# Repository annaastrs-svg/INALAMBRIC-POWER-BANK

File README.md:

-  FLUX CASE ! -

this is an inalambric power bank that uses a coil and inductance theory for charging my iphone LOL

I made this project because moustly I dont have battery or a cable, sooo a power bank that does not need non of them is the soloution yeyy 

PAG OF FLUX CASE (fotos , tutorial and more)
https://annaastrs-svg.github.io/Flux-Page-/

--

- PCB -

-eschematic -

-pcb -

-3d-

-BOM -

- CAD -

- 

WIRES ! 

MH-CD42 - USBC . 
VIN - VBUS ,
GND - GND ,

MH-CD42 - BTN . 
KEY - (+) , 
GND - (-) ,

MH-CD42 - COIL . 
VOUT - (+) ,
GND - (-) ,

MH-CD42 - BATTERY .
BAT - (+) , 
GND - (-) ,

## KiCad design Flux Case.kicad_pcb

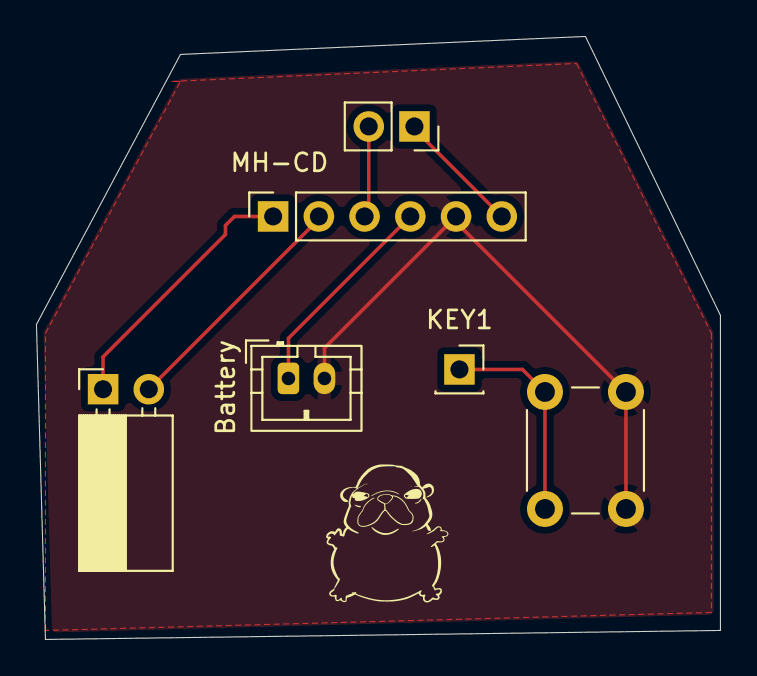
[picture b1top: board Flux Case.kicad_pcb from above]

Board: 2 copper layers, 38.0 x 33.5 mm, 6 parts (0 on the bottom side), 7 nets.

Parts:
Battery: Battery_Cell; JST_PH_B2B-PH-K_1x02_P2.00mm_Vertical
J1: USBC; PinSocket_1x02_P2.54mm_Horizontal
J2: Qi; PinSocket_1x02_P2.54mm_Vertical
KEY1: Conn_01x01_Pin; PinSocket_1x01_P2.54mm_Vertical
MH-CD: Conn_01x06; PinSocket_1x06_P2.54mm_Vertical
SW1: SW_Push; SW_PUSH_6mm_H4.3mm

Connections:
unnamed: Battery.1 (+), MH-CD.4
unnamed: Battery.2 (-), MH-CD.5, SW1.1
unnamed: J1.1, MH-CD.1
unnamed: J1.2, MH-CD.2
unnamed: J2.1, MH-CD.6
unnamed: J2.2, MH-CD.3
unnamed: KEY1.1 (Pin_1_1), SW1.2

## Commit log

2026-06-02 PCB DESIGN
2026-06-02 Add README for inalambric power bank project
    Added detailed description of the inalambric power bank project, including components, wiring instructions, and CAD image.
2026-06-02 Create tutorial for assembling power bank
    Added detailed building tutorial for power bank assembly and testing procedures.
2026-06-03 better tutorial jejeje
2026-06-12 Flux Case PCB
2026-06-12 Flux Case Schematic
2026-06-12 Flux Case KiCad files
    it have all the files (also theres onther file of othe project iinside that i cant take out )
2026-06-12 Fluz Case Gerber Files . zip
2026-06-12 BOM . CSV
2026-06-12 FLUX CASE .STEP
